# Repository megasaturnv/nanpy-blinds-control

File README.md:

# nanpy-blinds-control
Python program which performs actions depending on sunset and sunrise times

It controls an Arduino via the serial port with Nanpy: https://github.com/nanpy/nanpy

KiCad circuit board schematics are available in /blindsControlKiCad/

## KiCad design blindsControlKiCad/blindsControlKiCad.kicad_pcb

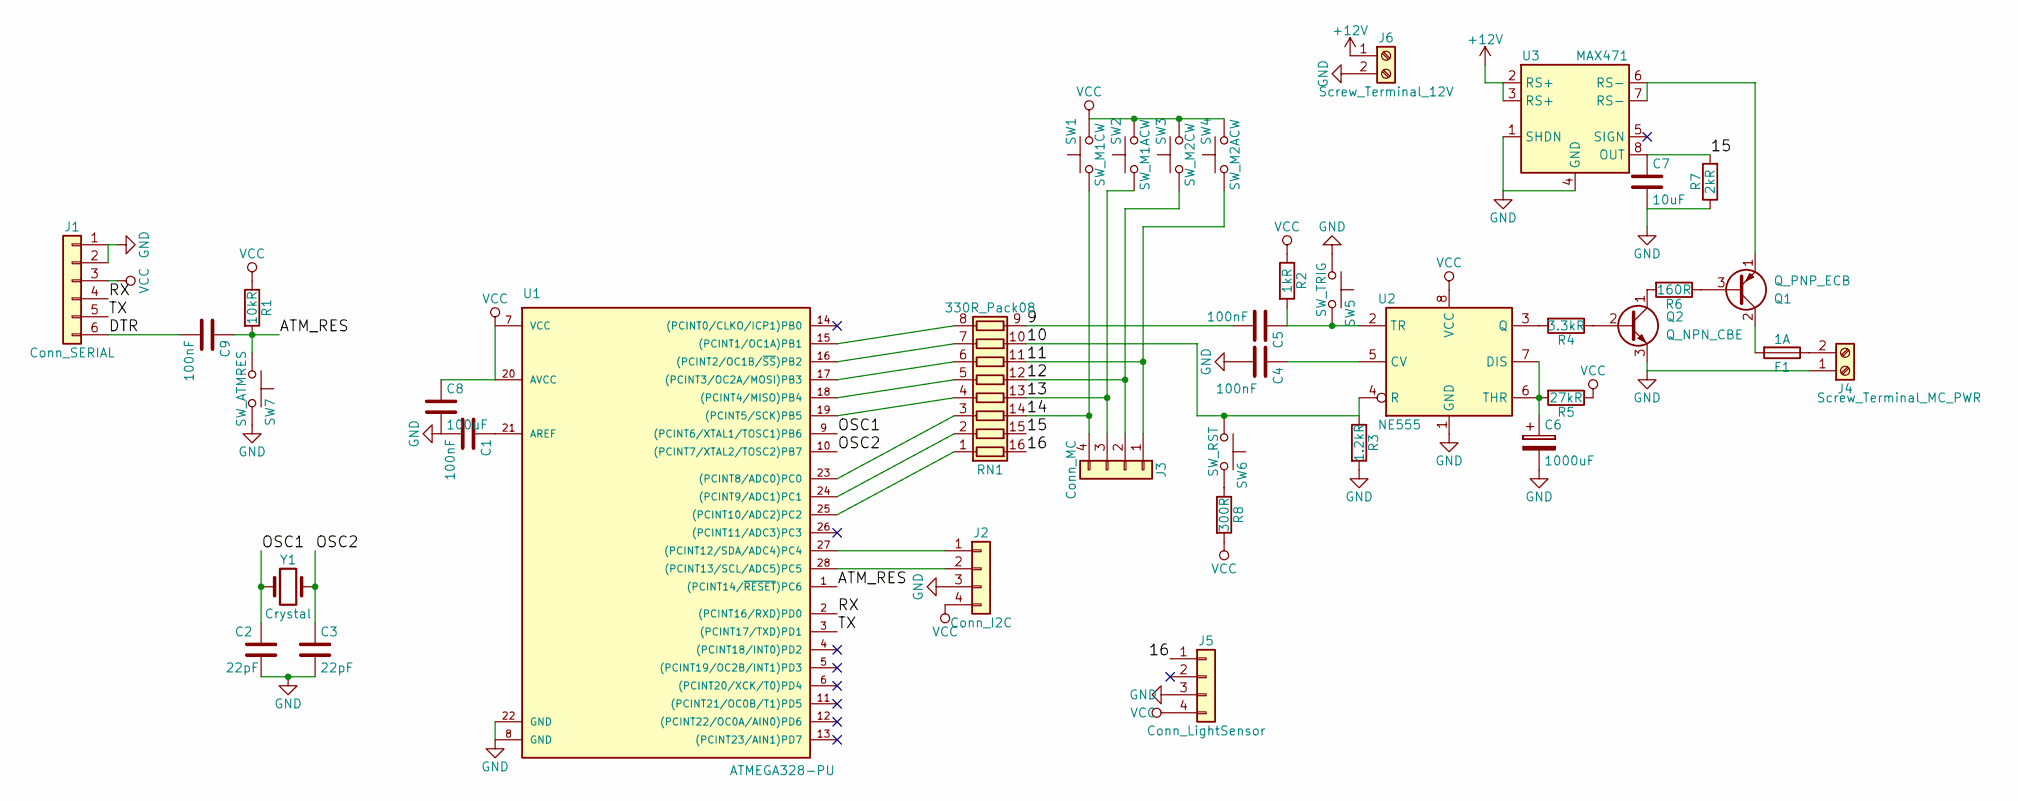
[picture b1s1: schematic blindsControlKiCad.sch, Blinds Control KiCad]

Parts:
C1, C4: 100nF; C_Disc_D3.0mm_W1.6mm_P2.50mm
C2, C3: 22pF; C_Disc_D3.0mm_W1.6mm_P2.50mm
C5, C9: 100nF; C_Disc_D4.3mm_W1.9mm_P5.00mm
C6: 1000uF; CP_Radial_D10.0mm_P5.00mm
C7: 10uF; CP_Radial_D5.0mm_P2.50mm
C8: 100uF; CP_Radial_D5.0mm_P2.50mm
F1: 1A; Fuseholder5x20_horiz_open_inline_Type-I
J1: Conn_SERIAL; Pin_Header_Angled_1x06_Pitch2.54mm
J2: Conn_I2C; Pin_Header_Straight_1x04_Pitch2.54mm
J3: Conn_MC; Pin_Header_Straight_1x04_Pitch2.54mm
J4: Screw_Terminal_MC_PWR; TerminalBlock_Phoenix_MKDS1.5-2pol
J5: Conn_LightSensor; Pin_Header_Straight_1x04_Pitch2.54mm
J6: Screw_Terminal_12V; TerminalBlock_Phoenix_MKDS1.5-2pol
Q1: Q_PNP_ECB; TO-126_Vertical
Q2: Q_NPN_CBE; TO-92_Inline_Wide
R1: 10kR; R_Axial_DIN0204_L3.6mm_D1.6mm_P5.08mm_Horizontal
R2: 1kR; R_Axial_DIN0207_L6.3mm_D2.5mm_P10.16mm_Horizontal
R3: 1.2kR; R_Axial_DIN0207_L6.3mm_D2.5mm_P10.16mm_Horizontal
R4: 3.3kR; R_Axial_DIN0207_L6.3mm_D2.5mm_P10.16mm_Horizontal
R5: 27kR; R_Axial_DIN0207_L6.3mm_D2.5mm_P15.24mm_Horizontal
R6: 160R; R_Axial_DIN0207_L6.3mm_D2.5mm_P10.16mm_Horizontal
R7: 2kR; R_Axial_DIN0309_L9.0mm_D3.2mm_P12.70mm_Horizontal
R8: 300R; R_Axial_DIN0309_L9.0mm_D3.2mm_P12.70mm_Horizontal
RN1: 330R_Pack08; DIP-16_W7.62mm
SW1: SW_M1CW; SW_Tactile_Straight_KSA0Axx1LFTR
SW2: SW_M1ACW; SW_Tactile_Straight_KSA0Axx1LFTR
SW3: SW_M2CW; SW_Tactile_Straight_KSA0Axx1LFTR
SW4: SW_M2ACW; SW_Tactile_Straight_KSA0Axx1LFTR
SW5: SW_TRIG; SW_Tactile_Straight_KSA0Axx1LFTR
SW6: SW_RST; SW_Tactile_Straight_KSA0Axx1LFTR
SW7: SW_ATMRES; SW_Tactile_Straight_KSA0Axx1LFTR
U1: ATMEGA328-PU; DIP-28_W7.62mm
U2: NE555; DIP-8_W7.62mm
U3: MAX471; DIP-8_W7.62mm
Y1: Crystal; Crystal_HC49-4H_Vertical

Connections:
+12V: J6.1, U3.2 (RS+), U3.3 (RS+)
/9: C5.2, RN1.9 (R8.2)
/10: R3.1, RN1.10 (R7.2), SW6.1, U2.4 (R)
/11: J3.1, RN1.11 (R6.2), SW4.1
/12: J3.2, RN1.12 (R5.2), SW3.1
/13: J3.3, RN1.13 (R4.2), SW2.1
/14: J3.4, RN1.14 (R3.2), SW1.1
/15: C7.1, R7.2, RN1.15 (R2.2), U3.8 (OUT)
/16: J5.1, RN1.16 (R1.2)
/ATM_RES: C9.1, R1.2, SW7.1, U1.1 ((PCINT14/~RESET~)PC6)
/DTR: C9.2, J1.6
/OSC1: C2.1, U1.9 ((PCINT6/XTAL1/TOSC1)PB6), Y1.1
/OSC2: C3.1, U1.10 ((PCINT7/XTAL2/TOSC2)PB7), Y1.2
/RX: J1.4, U1.2 ((PCINT16/RXD)PD0)
/TX: J1.5, U1.3 ((PCINT17/TXD)PD1)
GND: C1.2, C2.2, C3.2, C4.2, C6.2, C7.2, C8.2, J1.1, J1.2, J2.3, J4.1, J5.3, J6.2, Q2.3 (E), R3.2, R7.1, SW5.1, SW7.2, U1.8 (GND), U1.22 (GND), U2.1 (GND), U3.1 (SHDN), U3.4 (GND)
unnamed: C1.1, U1.21 (AREF)
unnamed: C4.1, U2.5 (CV)
unnamed: C5.1, R2.2, SW5.2, U2.2 (TR)
unnamed: C6.1, R5.2, U2.6 (THR), U2.7 (DIS)
unnamed: F1.1, J4.2
unnamed: F1.2, Q1.2 (C)
unnamed: J2.1, U1.27 ((PCINT12/SDA/ADC4)PC4)
unnamed: J2.2, U1.28 ((PCINT13/SCL/ADC5)PC5)
unnamed: Q1.1 (E), U3.6 (RS-), U3.7 (RS-)
unnamed: Q1.3 (B), R6.1
unnamed: Q2.1 (C), R6.2
unnamed: Q2.2 (B), R4.1
unnamed: R4.2, U2.3 (Q)
unnamed: R8.1, SW6.2
unnamed: RN1.1 (R1.1), U1.25 ((PCINT10/ADC2)PC2)
unnamed: RN1.2 (R2.1), U1.24 ((PCINT9/ADC1)PC1)
unnamed: RN1.3 (R3.1), U1.23 ((PCINT8/ADC0)PC0)
unnamed: RN1.4 (R4.1), U1.19 ((PCINT5/SCK)PB5)
unnamed: RN1.5 (R5.1), U1.18 ((PCINT4/MISO)PB4)
unnamed: RN1.6 (R6.1), U1.17 ((PCINT3/OC2A/MOSI)PB3)
unnamed: RN1.7 (R7.1), U1.16 ((PCINT2/OC1B/~SS~)PB2)
unnamed: RN1.8 (R8.1), U1.15 ((PCINT1/OC1A)PB1)
VCC: C8.1, J1.3, J2.4, J5.4, R1.1, R2.1, R5.1, R8.2, SW1.2, SW2.2, SW3.2, SW4.2, U1.7 (VCC), U1.20 (AVCC), U2.8 (VCC)

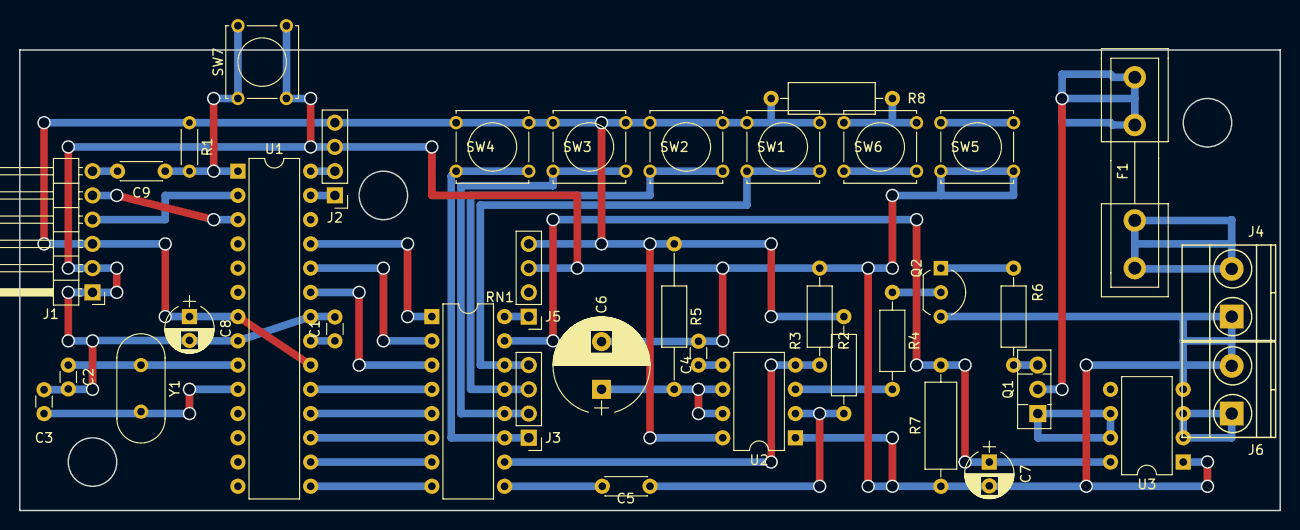
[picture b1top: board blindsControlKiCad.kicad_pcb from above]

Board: 2 copper layers, 132.1 x 48.3 mm, 38 parts (0 on the bottom side), 39 nets.

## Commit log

2018-03-03 Initial Upload
2018-03-03 Uploaded SVGs of circuit board
2018-03-03 Added SVGs
2018-03-04 Changed default log path
